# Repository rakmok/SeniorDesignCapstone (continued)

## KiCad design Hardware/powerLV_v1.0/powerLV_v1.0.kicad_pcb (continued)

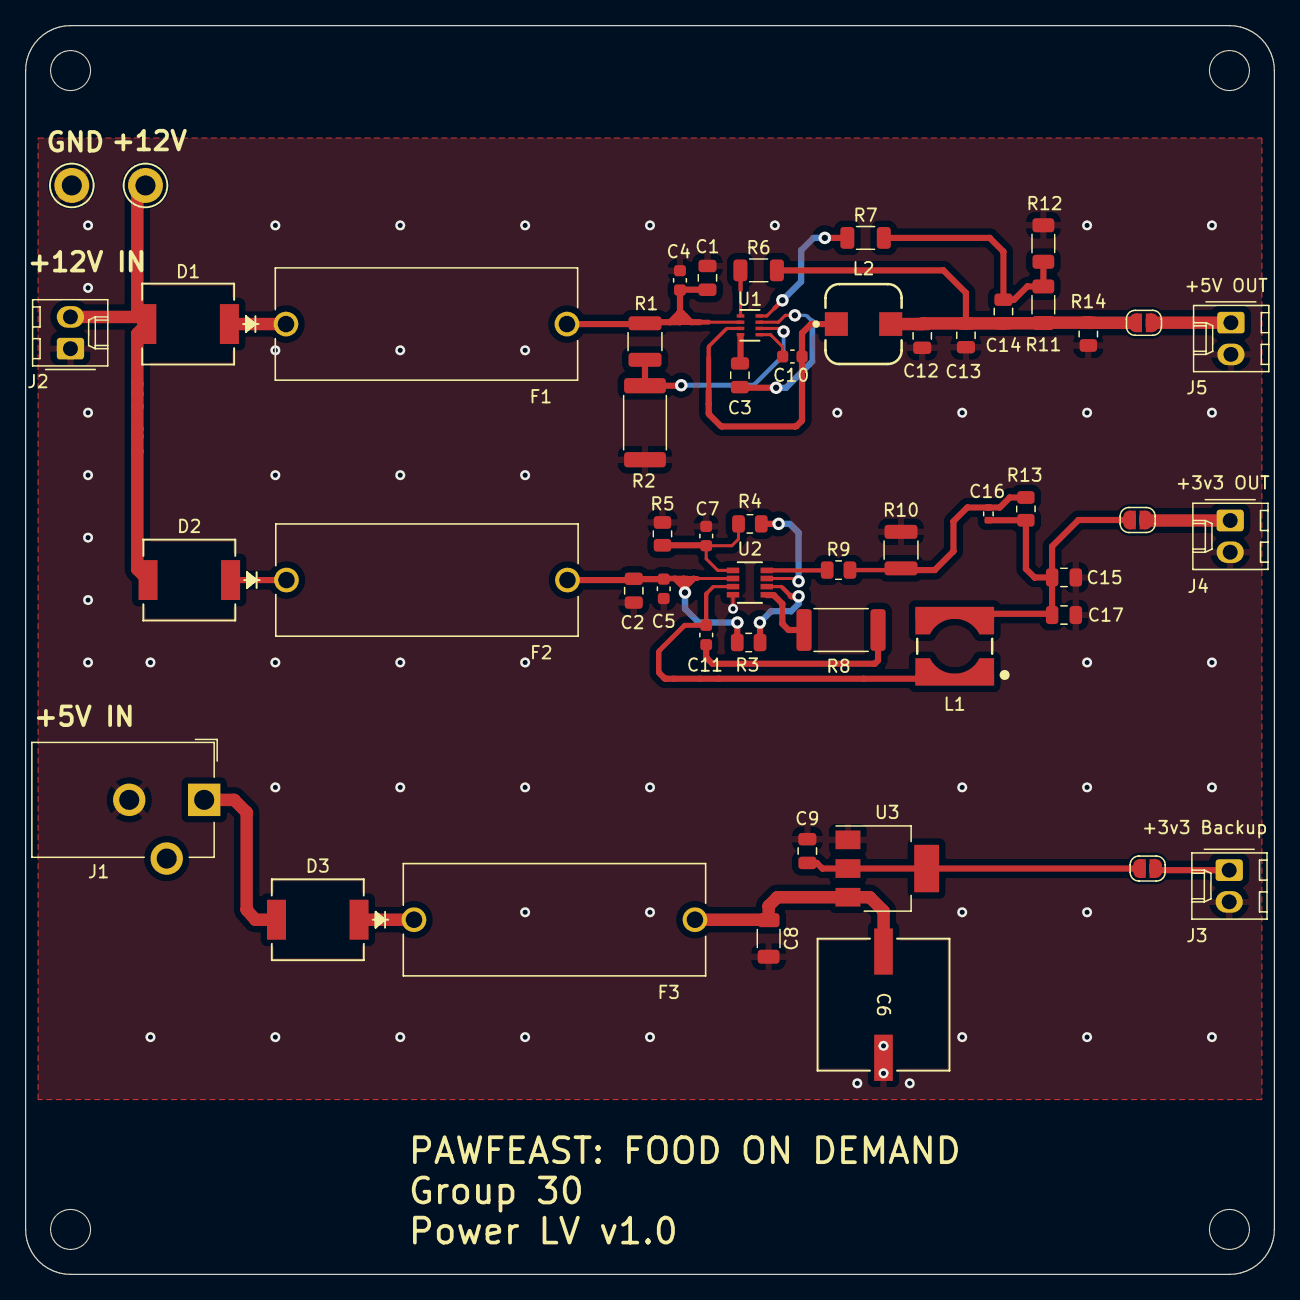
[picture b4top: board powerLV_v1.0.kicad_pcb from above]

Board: 2 copper layers, 100.0 x 100.0 mm, 56 parts (0 on the bottom side), 31 nets.

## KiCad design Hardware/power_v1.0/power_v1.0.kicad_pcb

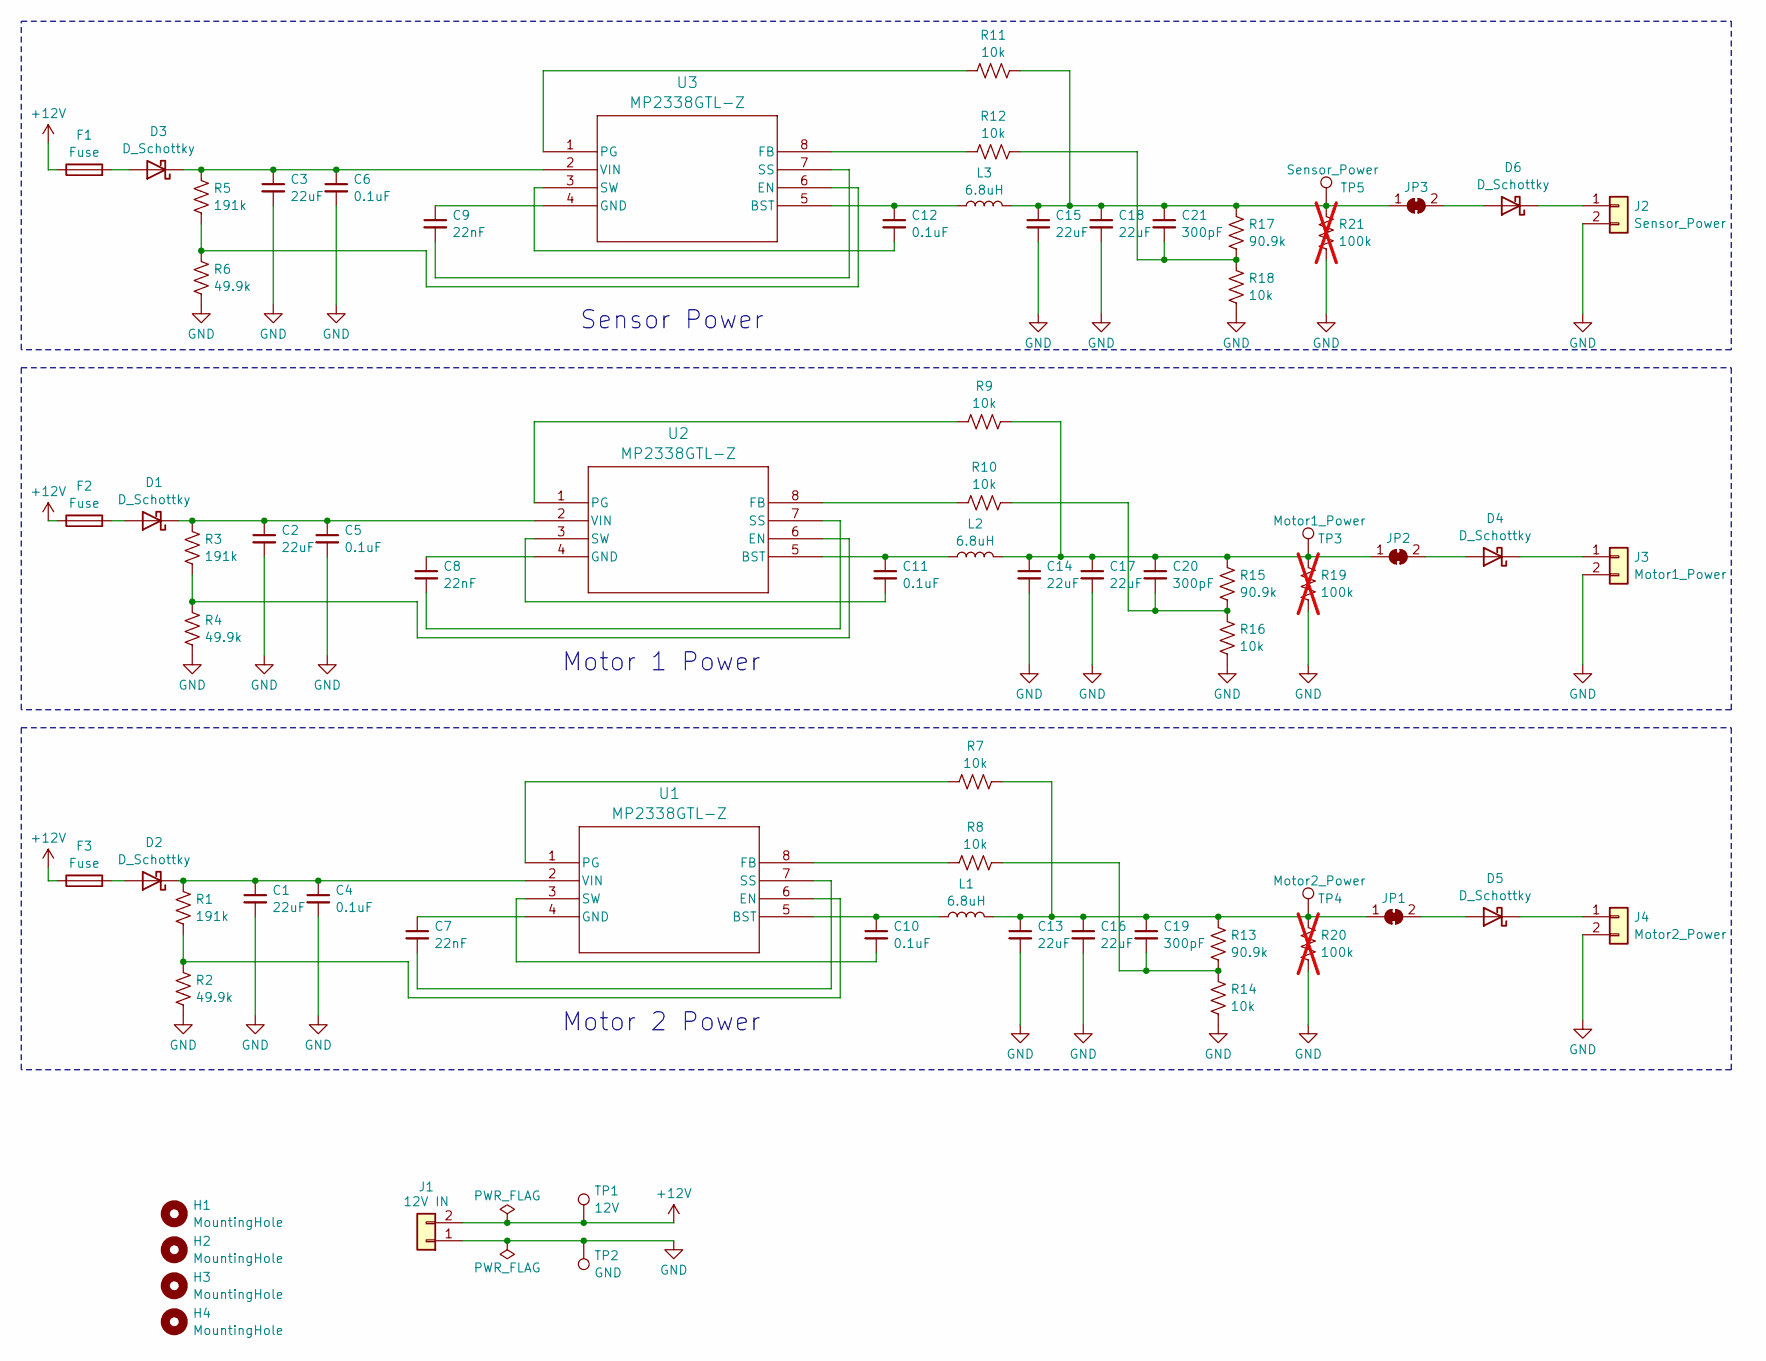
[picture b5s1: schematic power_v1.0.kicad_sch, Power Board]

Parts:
C1, C2, C3, C13, C14, C15, C16, C17, C18: 22uF; C_0805_2012Metric; MPN CL21A226MAYNNNE
C4, C5, C6, C10, C11, C12: 0.1uF; C_0603_1608Metric; MPN C0603C103F3GECAUTO
C7, C8, C9: 22nF; C_0805_2012Metric; MPN C0805C223F3GECAUTO
C19, C20, C21: 300pF; C_0805_2012Metric; MPN 08053C301JAT2A
D1, D2, D3, D4, D5, D6: D_Schottky; VS_30BQ015_M3_9AT; MPN VS-30BQ015-M3/9AT
F1, F2, F3: Fuse; FUSE_4628; MPN 36-4628-ND
H1, H2, H3, H4: MountingHole; MountingHole_3.2mm_M3; MPN NA
J1: 12V IN; Molex_KK-254_AE-6410-02A_1x02_P2.54mm_Vertical; MPN 1718560102
J2: Sensor_Power; Molex_KK-254_AE-6410-02A_1x02_P2.54mm_Vertical; MPN 1718560102
J3: Motor1_Power; Molex_KK-254_AE-6410-02A_1x02_P2.54mm_Vertical; MPN 1718560102
J4: Motor2_Power; Molex_KK-254_AE-6410-02A_1x02_P2.54mm_Vertical; MPN 1718560102
JP1, JP2, JP3: SolderJumper_2_Bridged; SolderJumper-2_P1.3mm_Bridged_RoundedPad1.0x1.5mm; MPN NA
L1, L2, L3: 6.8uH; WE-PD_6050R; MPN 7447786006
R1, R3, R5: 191k; R_1210_3225Metric; MPN ERJ-14NF1913U
R2, R4, R6: 49.9k; R_2512_6332Metric; MPN RMCF2512FT49K9
R7, R8, R9, R10, R11, R12, R14, R16, R18: 10k; R_1206_3216Metric; MPN HRG3216P-1002-B-T1
R13, R15, R17: 90.9k; R_1206_3216Metric; MPN RNCP1206FTD90K9
R19, R20, R21: 100k; R_0805_2012Metric; MPN RC0805FR-07100KL; not fitted
TP1: 12V; TestPoint_Keystone_5010-5014_Multipurpose; MPN 36-5010-ND
TP2: GND; TestPoint_Keystone_5010-5014_Multipurpose; MPN 36-5011-ND
TP3: Motor1_Power; TestPoint_Keystone_5010-5014_Multipurpose; MPN 36-5011-ND
TP4: Motor2_Power; TestPoint_Keystone_5010-5014_Multipurpose; MPN 36-5011-ND
TP5: Sensor_Power; TestPoint_Keystone_5010-5014_Multipurpose; MPN 36-5011-ND
U1, U2, U3: MP2338GTL-Z; SOT583_MP2338_MNP; MPN MP2338GTL-Z

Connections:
+12V: F1.1, F2.1, F3.1, J1.2, TP1.1
GND: C1.2, C2.2, C3.2, C4.2, C5.2, C6.2, C13.2, C14.2, C15.2, C16.2, C17.2, C18.2, J1.1, J2.2, J3.2, J4.2, R2.2, R4.2, R6.2, R14.2, R16.2, R18.2, R19.2, R20.2, R21.2, TP2.1
unnamed: C19.2, R8.2, R13.2, R14.1
unnamed: C20.2, R10.2, R15.2, R16.1
unnamed: C21.2, R12.2, R17.2, R18.1
unnamed: D1.2 (A), F2.2
unnamed: C2.1, C5.1, D1.1 (K), R3.1, U2.2 (VIN)
unnamed: D2.2 (A), F3.2
unnamed: C1.1, C4.1, D2.1 (K), R1.1, U1.2 (VIN)
unnamed: D3.2 (A), F1.2
unnamed: C3.1, C6.1, D3.1 (K), R5.1, U3.2 (VIN)
unnamed: D4.2 (A), JP2.2 (B)
unnamed: D4.1 (K), J3.1
unnamed: D5.2 (A), JP1.2 (B)
unnamed: D5.1 (K), J4.1
unnamed: D6.2 (A), JP3.2 (B)
unnamed: D6.1 (K), J2.1
unnamed: C13.1, C16.1, C19.1, JP1.1 (A), L1.2, R7.2, R13.1, R20.1, TP4.1
unnamed: C14.1, C17.1, C20.1, JP2.1 (A), L2.2, R9.2, R15.1, R19.1, TP3.1
unnamed: C15.1, C18.1, C21.1, JP3.1 (A), L3.2, R11.2, R17.1, R21.1, TP5.1
unnamed: C10.1, L1.1, U1.5 (BST)
unnamed: R1.2, R2.1, U1.6 (EN)
unnamed: R8.1, U1.8 (FB)
unnamed: C7.1, U1.4 (GND)
unnamed: R7.1, U1.1 (PG)
unnamed: C7.2, U1.7 (SS)
unnamed: C10.2, U1.3 (SW)
unnamed: C11.1, L2.1, U2.5 (BST)
unnamed: R3.2, R4.1, U2.6 (EN)
unnamed: R10.1, U2.8 (FB)
unnamed: C8.1, U2.4 (GND)
unnamed: R9.1, U2.1 (PG)
unnamed: C8.2, U2.7 (SS)
unnamed: C11.2, U2.3 (SW)
unnamed: C12.1, L3.1, U3.5 (BST)
unnamed: R5.2, R6.1, U3.6 (EN)
unnamed: R12.1, U3.8 (FB)
unnamed: C9.1, U3.4 (GND)
unnamed: R11.1, U3.1 (PG)
unnamed: C9.2, U3.7 (SS)
unnamed: C12.2, U3.3 (SW)

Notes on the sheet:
Motor 2 Power
Motor 1 Power
Sensor Power

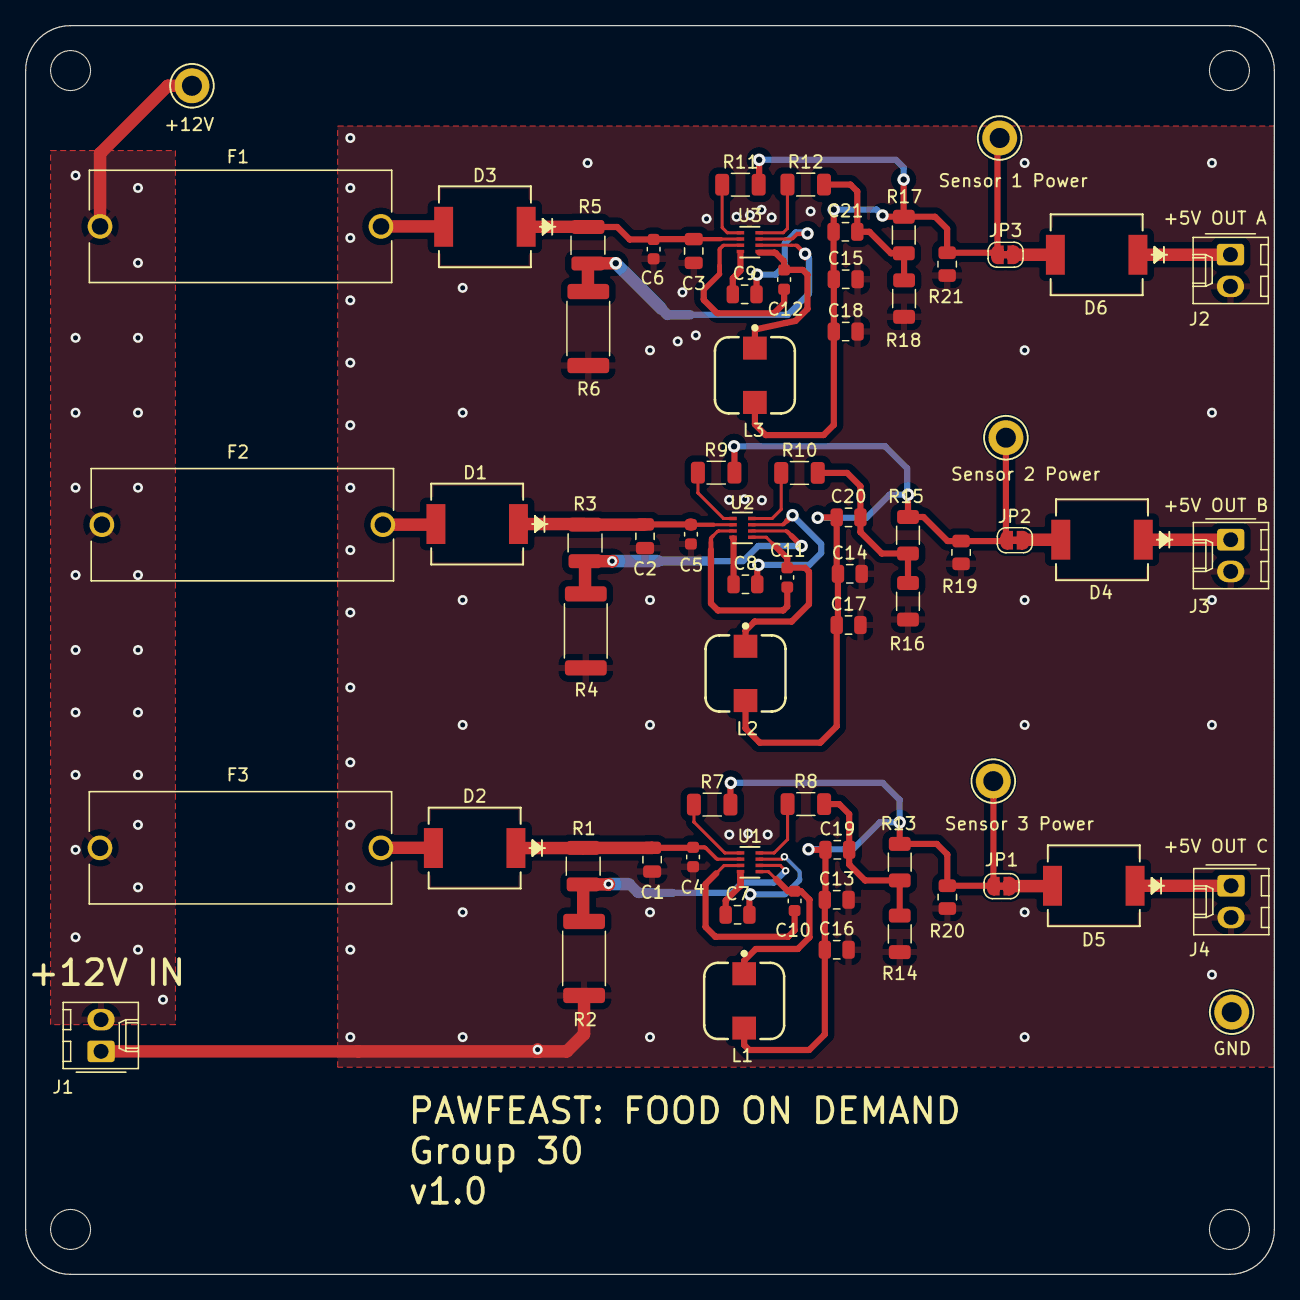
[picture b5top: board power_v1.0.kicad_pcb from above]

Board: 2 copper layers, 100.0 x 100.0 mm, 73 parts (0 on the bottom side), 41 nets.

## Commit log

2025-01-23 Initial setup of KiCAD libraries and members digital notebooks
2025-01-23 added an idea for the motivation
2025-01-23 added first meeting notes
2025-01-28 Update meeting log
2025-01-28 next notebook entry
2025-01-29 updated md file to match new project proposal
2025-02-04 added entry for 02/03 and removed other two notebooks from my branch as they are redundant
2025-02-11 updated journal
2025-02-11 2_11 new Update arash.md
2025-02-15 meeting entry update from yesterday and added statement of objective for next two meetings
2025-02-19 updating journal with some images
2025-02-19 updated block diagram
2025-02-20 Updating plan for next week
2025-02-20 post merge conflict
2025-02-25 notebook update
2025-02-25 created power and brain boards. Power has three regulators which output 5V for the motors/sensor, while brain will have the MCU, 3v3 regulator circuit, and level shifters among other things. Driver c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
2025-02-26 almost finished design of power board and working through design of brain board
2025-02-27 brain design pretty much done if RFID not needed
2025-02-28 finished part selection for power and almost done with part selection for brain--moving to layout next
2025-02-28 everything done on design and parts for first board run except for ADC; onto layout
2025-03-01 finished part selection and schematic for brain. Created RFID and Motor Driver boards
2025-03-02 brain fix and almost done with power board layout
2025-03-03 power board done
2025-03-04 updated journal for the week
2025-03-04 adding images
2025-03-04 fixing typo and adding another image
2025-03-05 pushing current
2025-03-05 Rename Notebooks/kathryn/Tables.png to Notebooks/kathryn/images/Tables.png
2025-03-05 Rename Notebooks/kathryn/feeding_times.png to Notebooks/kathryn/images/feeding_times.png
2025-03-05 Rename Notebooks/kathryn/history.png to Notebooks/kathryn/images/history.png
2025-03-05 Rename Notebooks/kathryn/Databases.png to Notebooks/kathryn/images/Databases.png
2025-03-05 Rename Notebooks/kathryn/pets.png to Notebooks/kathryn/images/pets.png
2025-03-05 Rename Notebooks/kathryn/petfood_weight.png to Notebooks/kathryn/images/petfood_weight.png
2025-03-05 Rename Notebooks/kathryn/users.png to Notebooks/kathryn/images/users.png
2025-03-05 log in, create user, log out, create pet all work. We now have the log in page and the dashboard page
2025-03-05 pushing current, need to make prettier, add feeding times work. Need to add history capabilties, this is more dependent on the ESP32 though
2025-03-07 RFID board schematic done, antenna head created in the layout
2025-03-07 updated entry and made the notebook easier to read
2025-03-07 updated entry
2025-03-07 fixing filepath issue
2025-03-07 changed it so only the notebook is present in the notebook's branch
2025-03-09 RFID schematic done
2025-03-10 made motor driver layout base and moved brain power to a separate board
2025-03-10 instead of an onboard power, I decided to make a separate board for just brain power--essentially a second power board.
2025-03-10 entry for today
2025-03-10 started brain layout, can definitely be done in the 100x100 mm space
2025-03-11 Halfway done with the brain layout--had to fix some issues from the schematic and relink designators. I also added an md file in the Hardware library that specifies how someone can link the Solar Car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
2025-03-11 made the readme a little easier to understand.
2025-03-11 added an entry for today
2025-03-11 updated the main readme
2025-03-11 Rename Arduino_IR.cpp to Arduino_PS.cpp
2025-03-12 more than halfway done with brain, optimizing routing
2025-03-12 new entry
2025-03-13 working on brain layout
2025-03-13 brain done! except for stitching vias
2025-03-13 done with brain v1
2025-03-13 updated motor driver
2025-03-25 fix merge conflict
2025-03-31 small change to powerLV
2025-04-05 changed LV
2025-04-05 updated motor
    yes
2025-04-06 second version of brain
2025-04-06 adding history image
2025-04-10 pushing successful communication between the esp and server with the routing needed for the dispense food logic (minus the button)
2025-04-14 pushing as of 4/19, with history
2025-04-15 Create ESP32_RFID_PS_LC.cpp
    This is the current integrated working code for the WIFI, RFID, PS, and LC. all routing is completed on the server end for the WIFI RFID and PS.
    - Need to differentiate the load cell readings and when they are pressed
    - Need to handle processing for server side of load cell to push a notification to history
2025-04-16 small fix to LV board
2025-04-17 pushing updates, this includes the project page, routing and small corrections for history
2025-04-17 pushing the project page, forgot
2025-04-17 pushing all the pictures
2025-04-17 pushing the fixed images
2025-04-17 update journal
2025-04-17 updated Lab notebook
2025-04-17 added load cell files
    sketch16 differentiates on address
    test1_adc is adafruit code just wired to gpio
2025-04-18 creating PDS board and update other boards
2025-04-19 PDS done
2025-04-19 gerbers for PDS
2025-04-19 fixed silkscreens + readability on PDS
2025-04-19 updated journal and added PDS images
2025-04-24 pushing all UI updates
2025-04-26 the ESP32 code (current) and shortened. Shortened (v2) has not been tested yet, but has the comments of changes needed to work
2025-04-27 pushing current working code
2025-04-27 pushing working consolidated
2025-04-28 push code, this is the updated code w comments of things to do
2025-04-28 added button and motor code, need to test it
2025-04-29 most recent code
2025-04-30 pushing the demo code and updated notebook
2025-05-01 just for git to be happy
2025-05-04 partially updated notebook, need to finish adding references and images
2025-05-04 added history page
2025-05-05 merging user interface
2025-05-05 Create . placeholder
2025-05-05 add html pages
2025-05-05 cleaning repo
2025-05-07 added a link to the demo video and some files from our project
2025-05-07 needed to do a git filter-repo cause I added a file that was too big
2025-05-07 fixing ReadME
2025-05-07 everything should show up now
2025-05-07 fixing YouTube link
2025-05-08 push updatas
2025-05-09 adding notebook
2025-05-09 uploading images
2025-05-10 notebook added correctly
